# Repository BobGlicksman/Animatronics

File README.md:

# OVERVIEW.
This project developed an animatronic head.  The head is capable of detecting and tracking motion in its field of view and of controlling
an eye mechanism to "wake-up" and track this motion.  The head can also play various recorded voice clips and move its mouth to follow the 
audio in a "convincing manner".  The head can detect various events and select an appropriate voice clip to play in response to the event.

See the Overview document in the root folder of this repository for further details.

## Motivation.

This project was designed to explore various aspects of animatronics, including three specific technologies:

1. **TOF Sensor:**  The VL53L5CX intelligent sensor 
(https://www.sparkfun.com/sparkfun-qwiic-mini-tof-imager-vl53l5cx.html)
contains a matrix of SPAD diodes that detect the time-of-flight of infrared light
reflected off an object to compute the distance to that object.  The sensor can report out an 8 x 8 array of distance 
measurements up to 15 times per second, making it a "poor man's LIDAR".

2.  **Animatronic Eye Mechanism:**  We used an eye mechanism built from this project:
https://www.instructables.com/Simplified-3D-Printed-Animatronic-Dual-Eye-Mechani/ of Nilheim Mechatronics. 
They have a YouTube channel: https://goo.gl/7Cle6h. In June 2024, Will released a new version of the 3D files that 
snaps together - no screws! https://www.youtube.com/watch?v=uzPisRAmo2s.

3.  **Voice and Mouth Control:**  We use a DFPLayer Mini MP3 module from DFRobotics 
(https://www.dfrobot.com/product-1121.html?srsltid=AfmBOornrlH_d-dh73ndTnoJ0Bhm0fcPcsy0bjisI8v6idOF1iMq-ogo)
to play various audio clips that we recorded on a micro-SD card.  A custom-developed analog processing circuit
scales, filters and extracts the envelope from the audio signal and the sampled envelope undergoes further real-time
software digital signal processing in order to drive a mouth servo in a "convincing manner".

## R & D.

In order to best perform the R&D associated with this project, a laser cut skeleton was developed so that the electronics and servos
can be positioned flexibly.  The "head" itself is 3D printed and flexibly attached to the skeleton via 3D printed ears with magnets
glued onto the mounting ears and the head pieces.  All CAD files for the laser cut and 3D printed pieces are included in this repository.

### Eye Movement.

In order to explore using the complex eye mechanism to create realistic eye movement scenarios, a flexible software system was
developed.

1. **Scene:**  A "scene" is the combination of the movements of the 6 eye servos to produce some specific effect, e.g. blink the eyes.

2. **Scenario:**  A "scenario" is a timed script of various scenes that produce some overall effect, e.g. a "sleepy dog" whose eyes 
periodically open just a crack and the eyeballs move around to survey the landscape, and then the eyes close and the dog goes 
back to sleep.

Scenes and Scenarios can be easily custom-defined and combined to create a wide variety of overall eye motion effects.  In addition,
scenarios are defined and implemented to effect eye movement to realistically track motion detected by the TOF sensor.

### Voice and Mouth Movement.

The mouth control electronics can play pre-recorded MP3 voice clips under software command by the onboard microcontroller.
A custom-designed analog signal processing circuit provides the microcontroller's A/D converter with analog signals that 
it can sample and process digitally.

1. **Scaled audio:**  the left audio MP3 player channel is shifted and scaled to be within the microcontroller's A/D 
converter range of 0 - 3.3 volts.  The signal is also filtered to a 3.3 KHz bandwidth (telephone audio quality) so 
that the microcontroller can sample this signal at 8 KHz (> the Nyquist criteria) and perform whatever digital signal 
processing is desired (at 125 microseconds per sample).
The analog AC signal is offset for the single supply A/D converter and the zero-offset voltage is provided on another A/D converter input
so that this offset can be subtracted (in software) from each sample.  These inputs are provided by the hardware but are not used
in the currently released software.

2. **Envelope Extraction:**  The scaled audio signal is further processed to extract the "envelope" of the audio signal by AM demodulation.
The bandwidth of the extracted envelope signal is approximately 40 Hz, which was empirically determined to preserve the full
information about the vocal elements of the voice clip while rejecting the "carrier" frequencies.  The envelope signal is 
connected to a 3rd A/D converter channel and the software samples this at 100 Hz.

The sampled envelope signal is processed in software to control the mouth servo.  In order to explore the nuances of controlling
the mouth servo to be "convincing", various configurable processing stages are provided in the released software:

a. **Linear and non-linear processing:**  The input envelope samples are scaled using either a linear or a non-linear scaling
algorithm.  The released software is configured for linear scaling, but realistic non-linear algorithms may be explored in
the future.

b. **Averaging:**  The 40 Hz envelope bandwidth and 100 Hz sampling are currently used to drive the mouth servo.  However,
1 to 5 samples may be averaged before being mapped to the servo drive.  The servo that we are using seems to work best
when driven without averaging the samples, and extreme averaging creates a noticeable lag between the audio and mouth movements.
However, averaging may be useful with other mechanical mouth linkages.

c.  **Servo scaling:** the processed samples are scaled to the desired servo range of travel before being used to control the mouth
servo.

### TOF Sensor.

The TOF sensor is very sophisticated and required a substantial amount of experimentation before we could use it successfully.
After figuring out what all of the controllable parameters do and how best to set them, we then worked on the actual application
of the sensor to this project.  The application includes:

1.  **Calibrating the room:**  Upon powering up the head, the room should be empty.  The software records the distance measurements
for the empty room so that it can later determine if anything has entered the room and respond to it.

2.  **Tracking movement:**  Tracking movement within the sensor's field of view turned out to be a challenge, as an 8 x 8 matrix of
distance measurements is complex.  In order to fix a point in space that is closet to the sensor, we had to combine both
spatial and temporal filters to reject "noise" in the data.  This filtering was necessary to produce non-jittery positioning
of the eyes to focus on the closest subject area in space.

3.  **Event detection:**  The software further processes the TOF data in order to detect various "events" for the head to
respond to:  (a) person(s) entering the TOF field of view, (b) person(s) leaving the TOF field of view, (c) person(s)
coming too close to the head.  Other events might be explored in the future.

# WHAT IS IN THIS REPOSITORY.

## Top Level.

1.  This README file.

2.  A photo of the Head.

3.  An Overview document describing this project in more detail.

4.  License information.

## Data Folder.

This folder contains digitized audio test files that were used with analysis and circuit simulation software to develop the analog
signal processing parameters for the circuit design.  These files are preserved for historical purposes and for further research;
they are not needed to implement the current animatronic head design.

## Documents Folder.

This folder contains the documentation for this project including several documents that detail the design, construction and operation of this project.

## Hardware Folder.

This folder contains information about the electronic design, including PCB CAD files and hookup data

## Legacy Folder.

This folder contains source code for various test programs that were used to exercise and research the various components
of the animatronic head prior to integrating the complete project.  These files are not part of the released head design but
are retained for possible use in future R&D.

## Mechanical Folder.

This folder contains the 2D and 3D CAD files for the skeleton, the head, the eye mechanism and other 3D printed mechanical
components of this project.

## Software Folder.

This folder contains source code for the two Particle Photon 1 microcontrollers used on this project.  The source code includes
the released operational code for each of the Photons, as well as some test and calibration code that needs to be used for
construction and calibration of the animatronic head.

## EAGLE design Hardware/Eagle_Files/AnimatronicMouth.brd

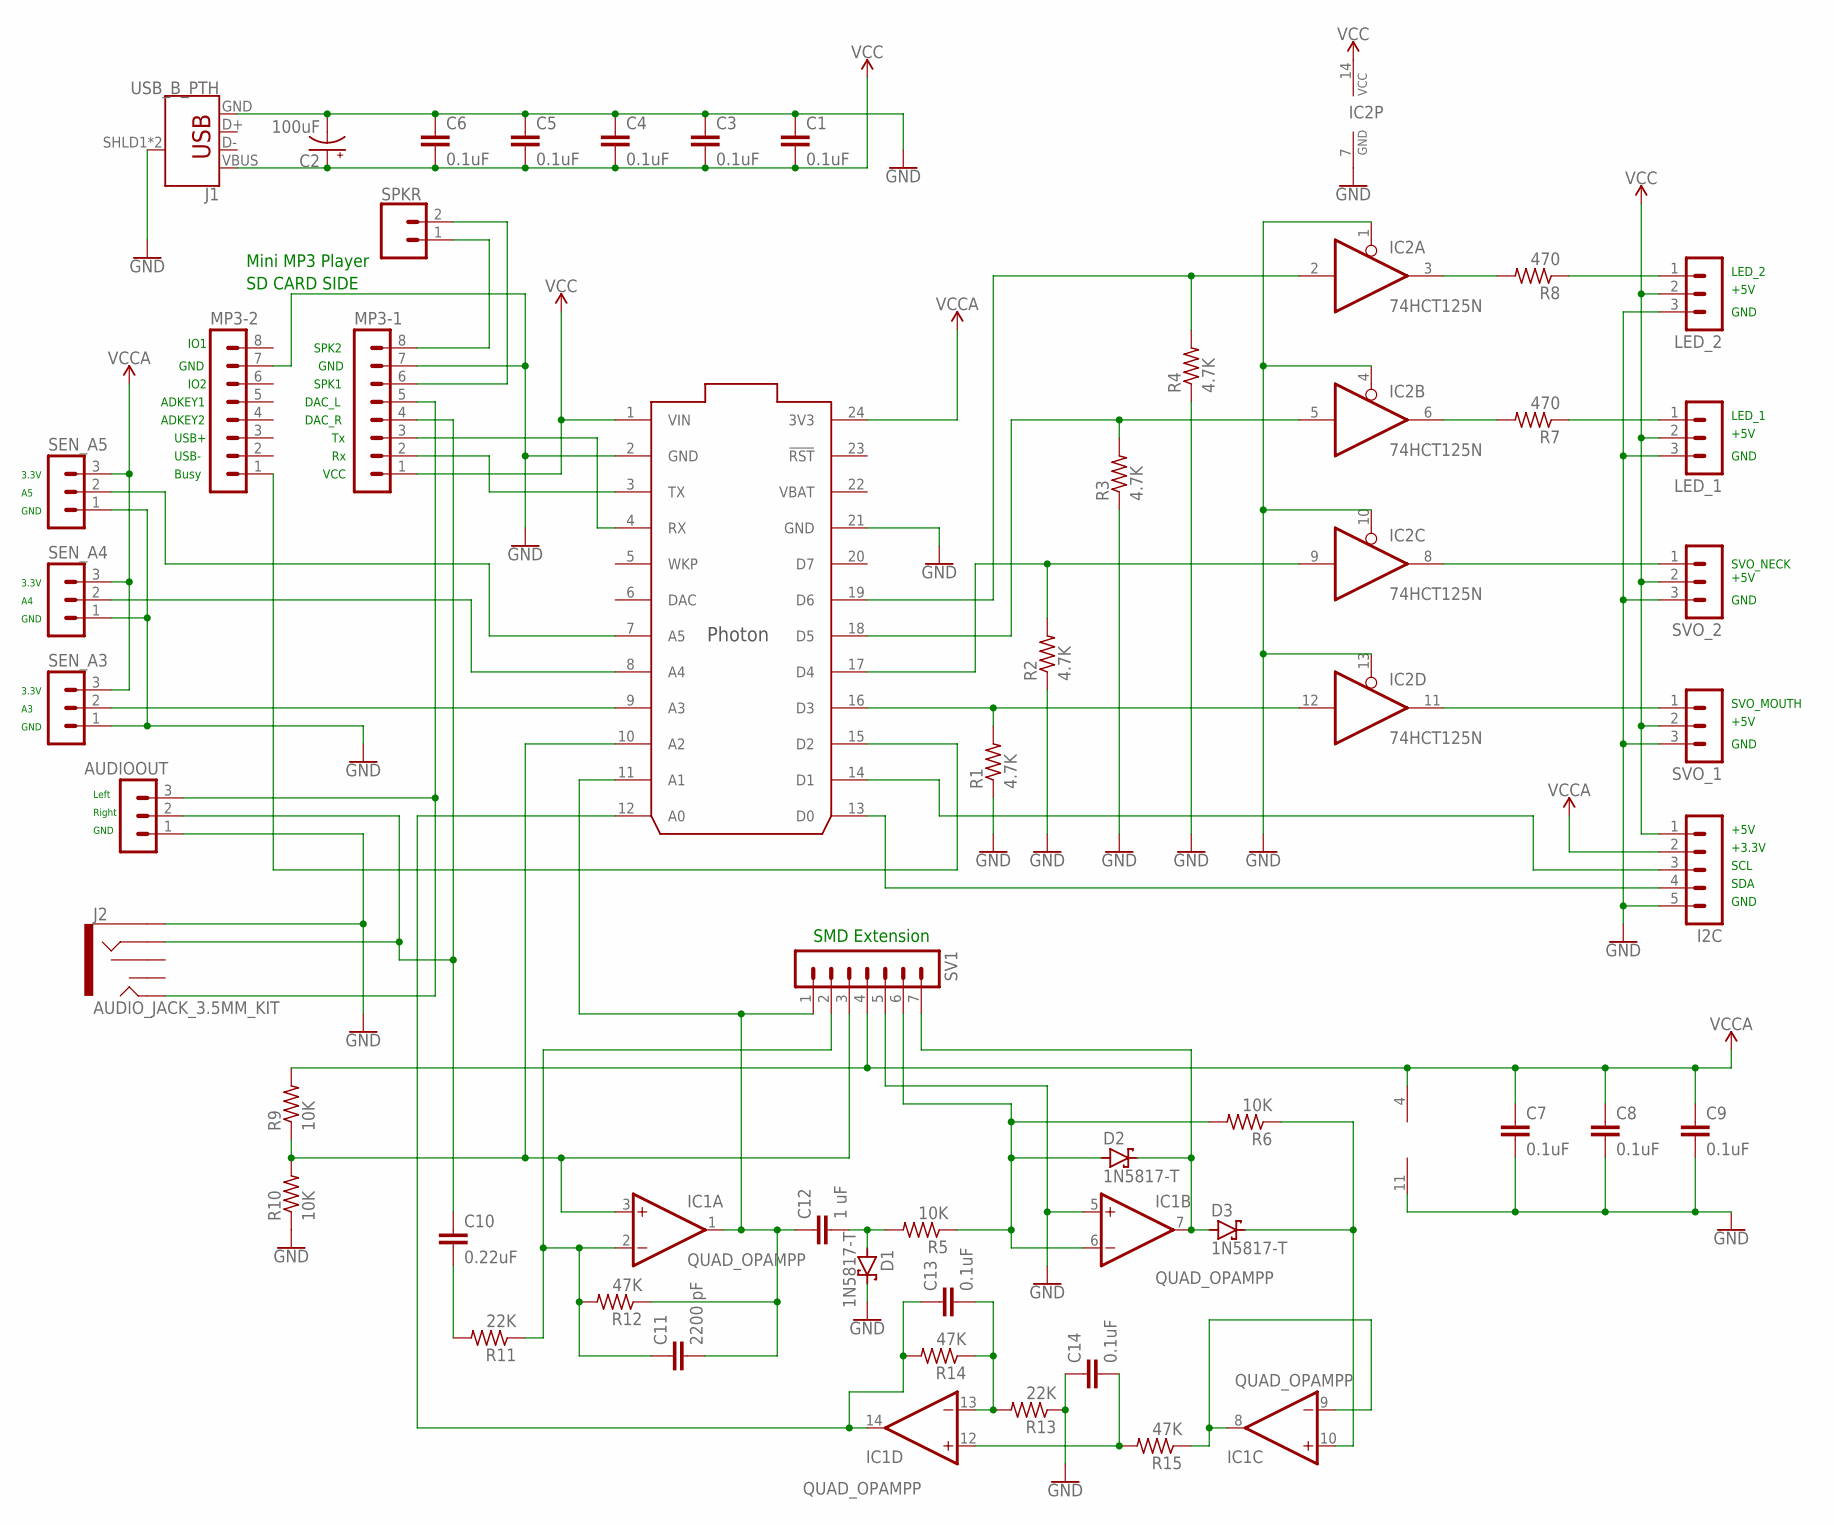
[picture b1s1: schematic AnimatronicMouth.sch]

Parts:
AUDIOOUT: MA03-1
C1, C3, C4, C5, C6, C7, C8, C9, C13, C14: 0.1uF; CAP-PTH-SMALL-KIT
C2: 100uF; CPOL-RADIAL-2.5MM-6.5MM
C10: 0.22uF; CAP-PTH-SMALL-KIT
C11: 2200 pF; CAP-PTH-SMALL-KIT
C12: 1 uF; CAP-PTH-SMALL-KIT
D1, D2, D3: 1N5817-T; DO41-7.6
I2C: MA05-1
IC1: QUAD_OPAMPP; DIL14
IC2: 74HCT125N; DIL14
J1: USB_B_PTH; USB-B-PTH
J2: AUDIO_JACK_3.5MM_KIT; AUDIO-JACK-KIT
LED_1, LED_2: MA03-1
MP3-1, MP3-2: MA08-1
R1, R2, R3, R4: 4.7K; 0309/12
R5, R6, R9, R10: 10K; 0309/12
R7, R8: 470; 0309/12
R11, R13: 22K; 0309/12
R12, R14, R15: 47K; 0309/12
SEN_A3, SEN_A4, SEN_A5: MA03-1
SPKR: CONN_023.5MM; SCREWTERMINAL-3.5MM-2
SV1: MA07-1
SVO_1, SVO_2: MA03-1
U$1: PHOTON_WITH_HEADERS; PHOTON

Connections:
GND: AUDIOOUT.1, C1.1, C2.2 (-), C3.1, C4.1, C5.1, C6.1, C7.2, C8.2, C9.2, C14.1, D1.C, I2C.5, IC1.5 (+IN), IC1.11 (V-), IC2.1 (OE), IC2.4 (OE), IC2.7 (GND), IC2.10 (OE), IC2.13 (OE), J1.GND, J1.SHLD1 (SHIELD), J1.SHLD2 (SHIELD), J2.SLEEVE, LED_1.3, LED_2.3, MP3-1.7, MP3-2.7, R1.1, R2.1, R3.1, R4.1, R10.1, R13.1, SEN_A3.1, SEN_A4.1, SEN_A5.1, SV1.5, SVO_1.3, SVO_2.3, U$1.2 (GND), U$1.21 (GND)
unnamed: IC2.12 (I), R1.2, U$1.16 (D3)
unnamed: IC2.5 (I), R3.2, U$1.18 (D5)
unnamed: IC2.9 (I), R2.2, U$1.17 (D4)
unnamed: IC2.2 (I), R4.2, U$1.19 (D6)
unnamed: IC2.11 (O), SVO_1.1
unnamed: LED_2.1, R8.1
unnamed: IC2.8 (O), SVO_2.1
unnamed: LED_1.1, R7.1
unnamed: IC2.6 (O), R7.2
unnamed: I2C.4, U$1.13 (D0)
unnamed: IC2.3 (O), R8.2
unnamed: MP3-1.6, SPKR.2
unnamed: C11.2, C12.1, IC1.1 (OUT), R12.1, SV1.1, U$1.11 (A1)
unnamed: IC1.3 (+IN), R9.1, R10.2, SV1.3, U$1.10 (A2)
unnamed: AUDIOOUT.2, C10.1, J2.RING, MP3-1.4
unnamed: C12.2, D1.A, R5.2
unnamed: D2.A, IC1.6 (-IN), R5.1, R6.2, SV1.6
unnamed: D2.C, D3.A, IC1.7 (OUT), SV1.7
unnamed: C13.1, IC1.14 (OUT), R14.2, U$1.12 (A0)
unnamed: C10.2, R11.2
unnamed: C11.1, IC1.2 (-IN), R11.1, R12.2, SV1.2
unnamed: MP3-1.2, U$1.3 (TX)
unnamed: MP3-1.3, U$1.4 (RX)
unnamed: MP3-2.1, U$1.15 (D2)
unnamed: AUDIOOUT.3, J2.TIP, MP3-1.5
unnamed: I2C.3, U$1.14 (D1)
unnamed: MP3-1.8, SPKR.1
unnamed: SEN_A5.2, U$1.7 (A5)
unnamed: D3.C, IC1.10 (+IN), R6.1
unnamed: SEN_A3.2, U$1.9 (A3)
unnamed: SEN_A4.2, U$1.8 (A4)
unnamed: C13.2, IC1.13 (-IN), R13.2, R14.1
unnamed: C14.2, IC1.12 (+IN), R15.2
unnamed: IC1.8 (OUT), IC1.9 (-IN), R15.1
VBAT: U$1.22 (VBAT)
VCC: C1.2, C2.1 (+), C3.2, C4.2, C5.2, C6.2, I2C.1, IC2.14 (VCC), J1.VBUS, LED_1.2, LED_2.2, MP3-1.1, SVO_1.2, SVO_2.2, U$1.1 (VIN)
VCCA: C7.1, C8.1, C9.1, I2C.2, IC1.4 (V+), R9.2, SEN_A3.3, SEN_A4.3, SEN_A5.3, SV1.4, U$1.24 (3V3)

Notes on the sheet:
VCC
DAC_R
DAC_L
SPK1
GND
SPK2
Busy
USB-
USB+
ADKEY2
ADKEY1
IO2
IO1
SD CARD SIDE
Mini MP3 Player
Right
Left
SDA
SCL
+3.3V
+5V
3.3V
SVO_MOUTH
SVO_NECK
LED_1
LED_2
SMD Extension

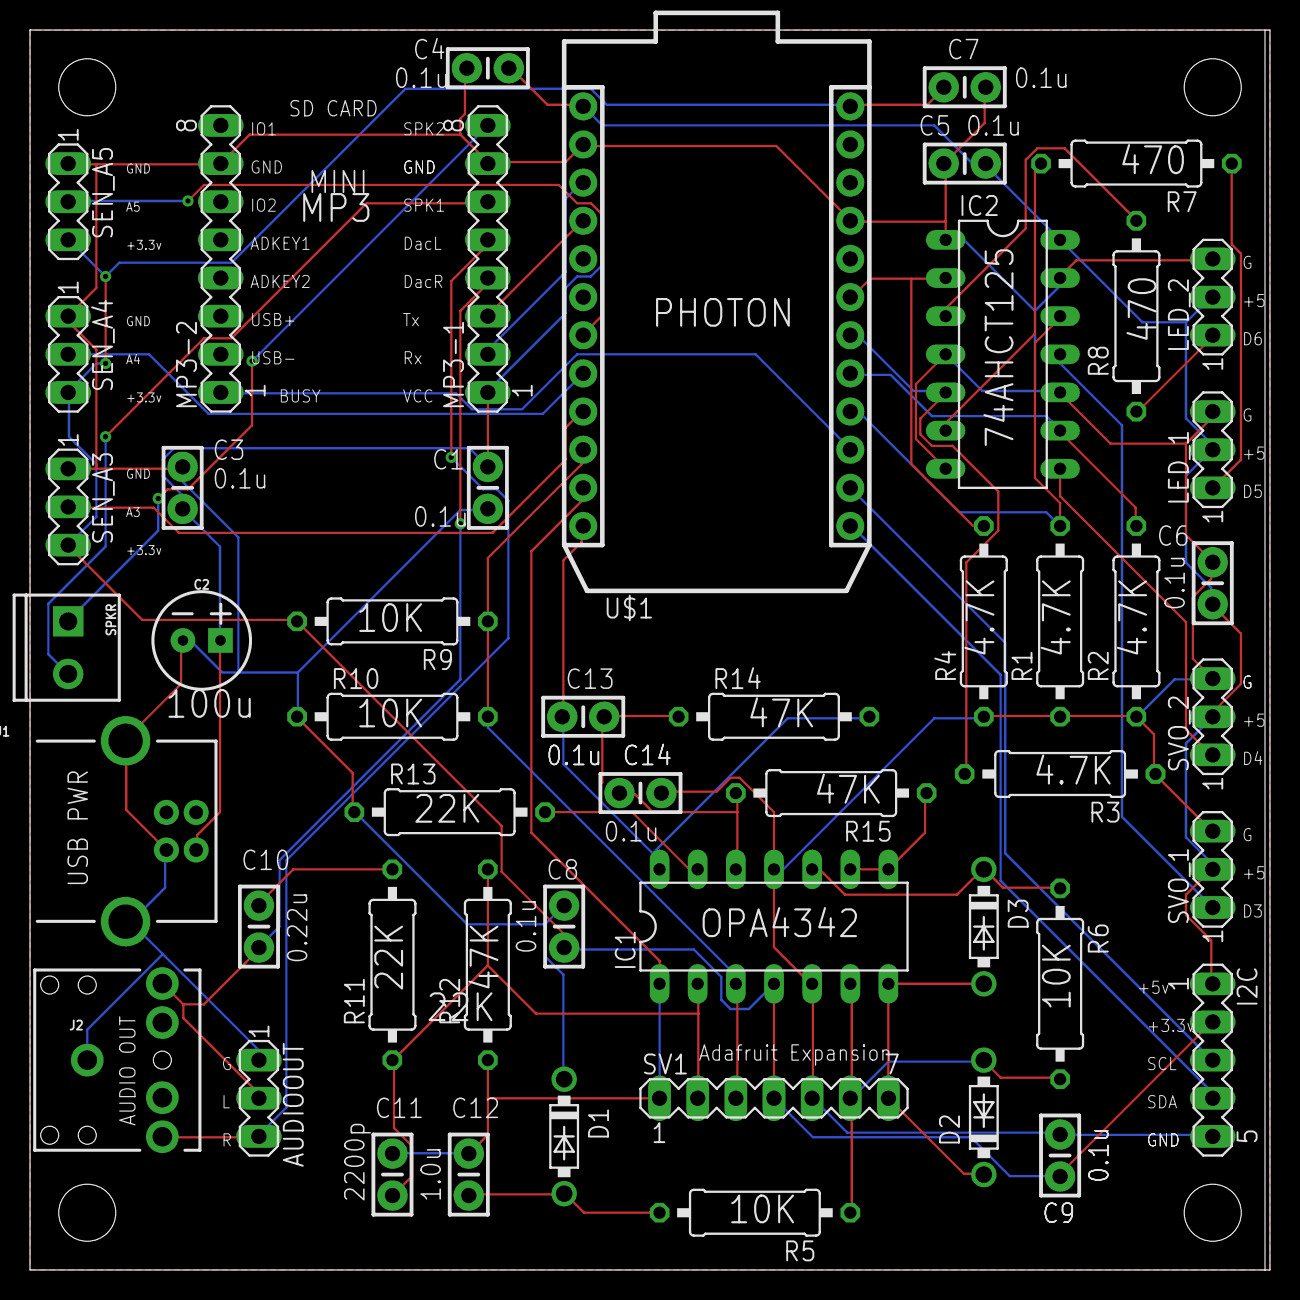
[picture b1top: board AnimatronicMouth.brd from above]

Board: 2 copper layers, 82.5 x 82.5 mm, 50 parts (0 on the bottom side), 37 nets.

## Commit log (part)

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2020-12-19 Create repository
    Added files for testing.
2020-12-19 Back to version 1.0
2020-12-19 Create AnimatronicMouth.mp4
    Video of mouth movement to .wav
2020-12-19 added MP3 player manual
2020-12-21 edited original per Bob's request
2020-12-21 Started MP3 mini payer work
2020-12-23 Mini MP3 player test firmware
2020-12-23 Updated Mini MP3 test Program
    Added a few comments and compiled/flased using Workbench
2020-12-24 Update MP3 Player Hookup.png
    Removed 4.7K resistor between MP3 Tx and Photon Rx because Photon Rx is 5 volt tolerant. I was concerned about the MP3 module internal regulator producing a highr (than 3.3 volt) signal from the 5 vo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
2020-12-25 DFRPlayerTestFullClip v1.0 created
    This program illustrates what is needed in order to play a clip on the mini MP3 player and then make sure that the first clip is complete before playing the nexty clip. It accounts for the MP3 player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
2020-12-25 Minor update
2020-12-30 Analog Processing V2
    New V2 circuit with analysis simulation data.
2020-12-30 Update Analog_Processor_V2_Analysis.pptx
    Added envelope filter freq response to ppt
2021-01-02 moved files to remove space in file path
2021-01-02 deleting the moved files
2021-01-07 corrected a comment
2021-01-08 Added test tone and other data
2021-01-09 v1 of AnimatronicEyes
2021-01-09 Software and Data for Analog HW testing
2021-01-10 added gitignore
2021-01-10 added .gitignore files and VS workspace
2021-01-10 reverted servo numbers from test values
2021-01-10 Publish test code
    DFPlayerControl.ino: test code for cloud
    control of the clip and the volume. The Particle console is used to select these values.
2021-01-10 Changed max clips for new SD card
2021-01-14 Create Photo_of_V2_circuit_in_breadboad.jpg
    Breadboard of V2 analog processing circuit. This breadboard circuit has been tested with the audio test files played through the moni MP3 player, controlled by a Photon. The output was verified using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
2021-01-16 test program to read analog and control servo
    This test program allows the user (via the Particle console) to set the mini MP3 player volume and clip number and play the selected clip. It samples the analog processing circuit envelope output eve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
2021-01-16 working version, still things to do
2021-01-16 Completed test firmware
    SoundMouthIntegrationtest.ino version 1.0 is released here.
2021-01-16 Added video clips
    Welcome_10ms_Samples.mp4 commands the servo every 10 ms. Welsome_20ms_Samples.mp commands the servo every 20 ms (averaging every 2 samples).
2021-01-16 Create Welcome_Clip_Settings.png
    Document the settings for the "best" welcome mouth performance.
2021-01-16 Now with sample scene list and better comments
2021-01-16 this workspace file works
2021-01-17 SoundMountIntegration V1.1
    Added constrain() so that servo doesn't peg. Toggle the D7 LED on each write to the servo so that the writing rate can be verified on a scope.
2021-01-18 move to better init PWM library
2021-01-18 changed from "head" to "puppet"
2021-01-18 added modifier to addScene
2021-01-19 converted speed to float so we can go slowly
2021-01-19 wake up sequence is pretty good. video on youtube
2021-01-21 More Test Voice Clips
    Added more voice clips for testing
2021-01-22 Update SoundMouthIntegrationTest.ino
    Version 1.2 -- added non-linear data scaling function using sqrt().
2021-01-23 Update SoundMouthIntegrationTest.ino
    firmware v1.3
    1. Added cloud function to set the non-linear processing type (0 = none, 1 = sqrt).
    2. Change mouth wide open defined constant to 105 deg vs 90 deg for more realism with my mechanical setup.
2021-02-12 Changed Servo Limits
    Changed servo limits for Jim's V1 "mouth"
2021-02-17 Added Eagle PCB Files
2021-02-18 Posted correct eagle files
2021-02-19 Updated Eagle Files
    Corrected Board Outline problem. This design is released for production.
2021-03-08 added workspace file
2021-03-08 Updated firmware
    Servo limits for the latest mouth version
2021-03-11 Updated Firmware (constants)
    Constants only; testing PCB for mouth and my eye setup.
2021-03-13 Update SoundMouthIntegrationTest.ino
    Set up mouth limits for the latest mouth mechanism. Closed + 90; Opened = 105.
2021-03-13 Update Analog_Processor_V2_Analysis.pptx
    Corrected annotation on block diagram for V2 design.
2021-03-14 Update settings.json
    Compiled for Photon "Animatronic2".
2021-03-14 Update SoundMouthIntegrationTest.ino
    Updated comments up front of the code to reflect the PCB and latest changes.
2021-03-20 Changed Photons for PC board testing
    There is no change to the code or the configuration other than changing Photons to get the code running on two PCBs,
2021-04-09 1.1 eyes roam, wake up; volatile in many places
2021-04-17 Added demo firmware
    Initial demo firmware - it is lacking the main state machine at this time.
2021-04-17 Demo play welcome message
    he default message when the PIR trips is the welcome message. Still need the state machine in loop().
2021-04-18 Update MN_Demo_Mouth.ino
    Incorporated the busy pin testing with busy hold delay.
2021-04-20 pre-release v0.1
    The code is complete and tested except for implementation of the pause button.
2021-04-21 Update MN_Demo_Mouth.ino
    Added button processing state machine and debounced button pressed function. Need to use this function to implement pause state.
2021-04-21 Update MN_Demo_Mouth.ino
    release version 1.0
2021-04-24 1.2 adds trigger from mouth controller
2021-04-24 added comment
2021-04-28 update to include eyes
2021-05-01 v1.2 idle eyes
2021-10-26 1.3 new eye constants now work
2021-10-31 1.4 kill switch; better wake up.
2021-11-06 Create adafruit_16channelServo_schem.png
    Added Adafruit 16 channel servo board schematic to hardware folder.
2021-11-08 Updated mouth constants
    Updated to fit the latest mechanical design.
2021-11-08 Reorganized repo
    Reorganized the repo to move all of the old legacy stuff to its own folder so as to not get confused with the released demo software. Also made sure that the mouth demo firmware had a proper workspac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
2021-11-15 Recalibrated eyes
    Used the latest version of the calibration code to recalibrate the eyes. Pasted the new calibration values into the eyes animation code.
2021-11-29 Update MN_Demo_Mouth.ino
    Tweeked the mouth limits for the best results on the rev 2 head.
2021-11-30 Update MN_Demo_Mouth.ino
    Latest mouth mechanical adjustments
2021-12-04 Update MN_Demo_Mouth.ino
    Randomly select the welcome (3/4) message or the pirate message (1/4)
2021-12-28 work in progress
2021-12-29 added structure for TOF sensor
2022-02-13 TOF is working
2022-02-13 after pull upstream main
2022-02-16 Modified for eyes event interface
2022-02-16 Uopdated comments
2022-02-16 Update settings.json
    Backed off to OS 3.0 because OS3.1 gives errors in the mini MP3 library.
2022-02-16 Update MN_Demo_Mouth.ino
    Working on the subscription
2022-02-17 Update MN_Demo_Mouth.ino
    corrected typos
2022-02-17 Update MN_Demo_Mouth.ino
    Added subscription to TOF_event and the handler function. The handler function just calls the newMounthEvent() function that can also be called directly from the console, for testing.
2022-02-17 Update MN_Demo_Mouth.ino
    Added error detection for out of range enumerated value.
2022-02-18 latest mp3 player library
    Tried to use the latest library, but it still compiles on ON3.0 but not on 3.1 or above due to library return errors.
2022-03-15 added mechanical files
2022-03-22 Update MN_Demo_Mouth.ino
    changed mouth servo limit constants for new 3D printed mouth bracket
2022-03-22 Update MN_Demo_Mouth.ino
    Update with new mouth limit constants for newly positioned mouth servo.
2022-04-11 eyes full range
2022-04-14 working
2022-04-14 Update MN_Demo_Mouth.ino
    Slight changes to mouth servo limits after remounting mouth servo with velcro.
2022-04-17 recalibrate
2022-04-28 Update MN_Demo_Mouth.ino
    version 1.3: updated the interface and added two new voice clips.
2022-04-28 New voice clips for head
    Added voice clips for too close ("backoff") and for normal leaving ("thanks").
2022-05-01 reverted to 1.6
2022-05-02 Added TOF event ptocessing
    version 1.7: added TOF event processing to AnimatronicEyes.ino
2022-05-06 New servo settings
    I repaired my eye mechanism and therefore recalibrated.
2022-05-13 Update AnimatronicEyes.ino
    bumped the version to 1.8 and fixed a minor typo in a comment.
2022-05-28 #defines for our different chin set ups
2022-05-28 Update MN_Demo_Mouth.ino
    Implemented #define for different mouth calibrations for Jim and for Bob
2022-05-30 no code changes, just leading tabs
2022-06-06 changed to .playMp3Folder
2022-06-06 audio files in new format
2022-06-10 Added latest voice clips
    Complete contents of microSD card with active clips in the MP3 subfolder, per v 1.5 of the mouth_demo code
2022-10-02 added .gitignore
2022-10-02 gitignore
2022-10-02 Update AnimatronicMouth.code-workspace
2022-10-04 removed Daisy clip
2022-10-05 personalities. mouth calibration cloud func.
2022-10-05 removed compile warnings
2022-10-05 audio clips
2022-10-05 update to gitignore
2022-10-05 bug fix line 174. numClips was one too large
2022-10-05 update of workspace
2022-10-08 moved audio files. updated gitignore
2022-10-08 moved audio files to SDCard foler
2022-10-10 changed constants for Jim's audio
2022-10-12 set two delay times to 0 at our meeting
2022-10-14 correct, amplified, audio files
2022-10-14 settings update
    for my photon, not jim's
2022-10-16 nlp 2 seems to work for jims clips
2022-10-16 set jims clips to nl2
2022-10-21 won't play same clip twice in a row
2022-10-23 Made Jim's personality #2
2022-10-28 better selection of personalities
2022-11-04 fix for corruption in personalities
2022-11-04 Update MN_Demo_Mouth.ino
    Select Bob's mouth configuration
2022-11-04 Create Jumper_settings_for_personalities.txt
    Added a short document of the jumer settings for each of 4 personalities.
2022-11-20 Made continuous display work better
2022-11-25 temporal filtering
2022-11-27 better temporal logging; POI must be closer
2022-11-29 better temporal filtering
2022-11-29 more of temporal filtering
2022-11-29 added cloud reset function for testing
2022-11-30 temporal filter requires same x,y
2022-11-30 1.9 with multiframe calibration and xy temporal
2022-12-01 adds back test for avgDist of zone
2022-12-01 Update AnimatronicEyes.ino
    changed version to 1.9
2022-12-01 fix so mouth gets goodbye events
2022-12-02 fix for goodbye while standing in front of head
2022-12-03 pass poi to processEvents
2022-12-03 included new globals.h
2022-12-03 the globals.h
2022-12-03 removed most warnings
2022-12-03 removed more warnings
2022-12-04 local variable renames in processEvents
2022-12-07 state machine as second algo for mouth events
2022-12-07 missed a file
2022-12-07 bug fix for repeated hello/goodbye
2022-12-08 bug fix: state machine conforms to diagram
2023-01-04 Recalibrated my eyes servos
    Recalibrated after repair
2024-06-19 Update README.md
    added link to new snap-only eye mech
2025-02-08 Update README.md
    Updated this file to reflect the current state of the project,
2025-02-08 Update README.md
    Corrected typo
2025-02-09 Added head photo
2025-02-09 Update README.md
    Minor editing
2025-02-10 Updated eye calibration
    Re-calibrated the eyes. Also documented the calibration procedure.
2025-02-13 Update eyeservosettings.h
    Re-calibrated the eyes.
2025-02-19 changes to DFPlayerMini so it compiles without warnings
2025-02-19 because these files are in the repo
2025-12-02 added armature dfx files
2025-12-15 Early Draft Docs
    Placeholders for final docs so that references are available for the Overview doc.
2025-12-16 Update Animatronic Head Electronic Hardware Document.pdf
    Version 1.1 with Jim's comments.
2025-12-18 Corrected typo
2025-12-19 Overview doc and updated README
2025-12-23 Update Animatronics_Overview_Document.pdf
    Incorporate Jim's changes
2025-12-28 head top
2025-12-28 speaker bracket
2025-12-28 brain and eye doc updates
2025-12-28 typo in title
2025-12-29 Update Animatronics_Mouth_Software_Description_Document.pdf
    Incorporated Jim's suggestions.
2026-01-09 update eye mech doc

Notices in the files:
Hardware/Eagle_Files/AnimatronicMouth.brd:
(c) 2021, TEAM PRACTICAL PROJECTS
All Rights Reserved
parts and their libraries:
Particle-Devices: Licensing: Designed by Particle.
SparkFun-Connectors: Licensing: Creative Commons ShareAlike 4.0 International - https://creativecommons.org/licenses/by-sa/4.0
